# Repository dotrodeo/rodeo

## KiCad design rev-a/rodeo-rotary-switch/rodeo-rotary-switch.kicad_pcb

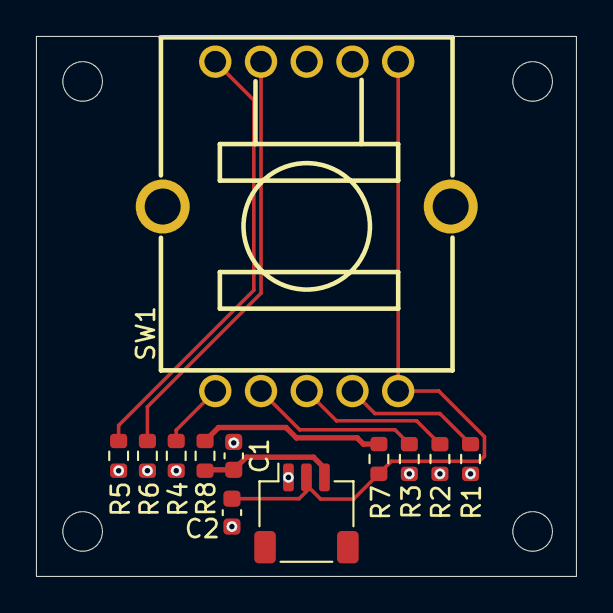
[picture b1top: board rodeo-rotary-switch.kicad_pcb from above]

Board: 2 copper layers, 30.0 x 30.0 mm, 12 parts (0 on the bottom side), 10 nets.

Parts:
C1, C2: 100n; C_0603_1608Metric
J1: Conn_01x03; JST_SH_SM03B-SRSS-TB_1x03-1MP_P1.00mm_Horizontal
R1, R8: 1K; R_0603_1608Metric
R2: 2.2K; R_0603_1608Metric
R3: 4.7K; R_0603_1608Metric
R4, R7: 10K; R_0603_1608Metric
R5: 22K; R_0603_1608Metric
R6: 47K; R_0603_1608Metric
SW1: SW-TH_SRBV141404

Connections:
3V3_D: R7.1, R8.1
GND: C1.1, C2.2, J1.1, R1.2, R2.2, R3.1, R4.1, R5.1, R6.1
unnamed: C1.2, J1.3, R8.2
unnamed: R1.1, SW1.2
unnamed: R2.1, SW1.3
unnamed: R3.2, SW1.4
unnamed: R4.2, SW1.5
unnamed: R5.2, SW1.6
unnamed: R6.2, SW1.7
OUTPUT: C2.1, J1.2, R7.2, SW1.1, SW1.10

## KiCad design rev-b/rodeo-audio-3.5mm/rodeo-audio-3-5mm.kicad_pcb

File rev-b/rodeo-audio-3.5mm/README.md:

# Rodeo audio jack board: 3.5 mm

Four stereo 3.5 mm TRS jacks for the motherboard's eight audio signals, on the
2×10 audio ribbon (motherboard J4). Passive apart from protection: every input
gets a series resistor and a clamp, every jack contact an ESD diode. The ribbon
contract is in [`rev-b.md`, "Audio interface and jack board"](../rodeo-motherboard/docs/rev-b.md#audio-interface-and-jack-board).

Designed 2026-10-14. A 1/4" variant will share this circuit with different
jacks. JLC stocks no right-angle 1/4" PCB jacks, so that board's jacks will be
hand-soldered.

```
            ┌──────────────── jack board ─────────────────┐
 ribbon     │                                             │   panel
 pin 2  ────┼── 100 Ω ──┬─────────────────── J2 tip       │   SEED OUT
 pin 4  ────┼── 100 Ω ──┼─┬───────────────── J2 ring      │
            │          TVS TVS                            │
 pin 6  ────┼───────────┬─────────────────── J3 tip       │   CODEC OUT
 pin 8  ────┼───────────┼─┬───────────────── J3 ring      │
            │          TVS TVS                            │
 pin 12 ────┼──┬────────── 470 Ω ─────────── J4 tip       │   SEED IN
 pin 14 ────┼──┼─┬──────── 470 Ω ─────────── J4 ring      │
            │ TVS TVS                                     │
 pin 16 ────┼──┬────────── 470 Ω ─────────── J5 tip       │   CODEC IN
 pin 18 ────┼──┼─┬──────── 470 Ω ─────────── J5 ring      │
            │ TVS TVS                                     │
 odd pins ──┼── GND ─────────────────────── all sleeves   │
            └─────────────────────────────────────────────┘
```

## Signals and levels

All eight signals are single-ended, about 4 Vpp at the jack, AC-coupled on the
motherboard side. Tip is left (channel 1 / A), ring is right (channel 2 / B).

A mono plug in a stereo jack grounds the ring: on an input the right channel
reads 0 V (firmware can copy left to right if it wants mono-to-both); on an
output it shorts the right output to ground, which the series resistors make
harmless (100 Ω here on the Seed outputs, 560 Ω on the motherboard for the codec).

## Connections

**J1, ribbon: 2×10 shrouded box header, DC3-2.54-20PAS (C2977593)**, the same
part as the motherboard's J4. Symbol `Connector_Generic:Conn_02x10_Odd_Even`,
footprint `Connector_IDC:IDC-Header_2x10_P2.54mm_Vertical`.

| Pin | Net | Pin | Net |
|---|---|---|---|
| 1, 3 … 19 | `GND` (all odd pins) | | |
| 2 | `AUDIO_OUT_1` | 12 | `JACK_IN_1` |
| 4 | `AUDIO_OUT_2` | 14 | `JACK_IN_2` |
| 6 | `CODEC2_OUT_A` | 16 | `CODEC2_IN_A` |
| 8 | `CODEC2_OUT_B` | 18 | `CODEC2_IN_B` |
| 10 | `+5V_A`: not used here, no connect | 20 | no connect |

**Jacks J2–J5: PJ-320D (C431535)**, the 3.5 mm stereo jack Rev A used. Symbol
`Connector_Audio:AudioJack4`, footprint
`Connector_Audio:Jack_3.5mm_PJ320D_Horizontal`. Pin R2 (the ring's switch
contact) is unused: no connect.

| Jack | Panel label | T (left) | R1 (right) | S |
|---|---|---|---|---|
| J2 | SEED OUT | R1 100 Ω from `AUDIO_OUT_1` | R2 100 Ω from `AUDIO_OUT_2` | `GND` |
| J3 | CODEC OUT | `CODEC2_OUT_A` direct | `CODEC2_OUT_B` direct | `GND` |
| J4 | SEED IN | R4 470 Ω to `JACK_IN_1` | R3 470 Ω to `JACK_IN_2` | `GND` |
| J5 | CODEC IN | R6 470 Ω to `CODEC2_IN_A` | R5 470 Ω to `CODEC2_IN_B` | `GND` |

**Protection: D1–D8, PESD3V3S1BA (C7472904)**, bidirectional 3.3 V ESD diodes,
SOD-323, 18 pF. Symbol `Device:D_TVS` (bidirectional, so orientation doesn't
matter), footprint `Diode_SMD:D_SOD-323`. Each to `GND`:

| Diode | Node | Diode | Node |
|---|---|---|---|
| D1 | J2 tip (at the jack) | D5 | `JACK_IN_2` (ribbon side of R3) |
| D2 | J2 ring (at the jack) | D6 | `JACK_IN_1` (ribbon side of R4) |
| D3 | J3 tip (at the jack) | D7 | `CODEC2_IN_B` (ribbon side of R5) |
| D4 | J3 ring (at the jack) | D8 | `CODEC2_IN_A` (ribbon side of R6) |

* **Inputs: resistor first, then the clamp.** ESD and any sustained
  out-of-range signal (a ±12 V Eurorack output) go through the 470 Ω before the
  diode clamps at about ±5.6 V, so the diode never sees more than
  (12 − 5.6) / 470 ≈ 14 mA and the motherboard side never more than ±5.6 V.
  R3–R6 are **0603** for the ESD pulse and the ≈90 mW of that worst case.
* **470 Ω on the inputs** costs ≈0.5 dB on the codec inputs (7.5 kΩ input
  resistor on the motherboard). The Seed's input impedance hasn't been measured,
  but it is several kΩ at least, so the loss there is similar or smaller.
* **Outputs:** the 3.3 V diode doesn't conduct below ±5 V, above the 4 Vpp
  (±2 V) full scale. 18 pF against the 100 Ω/560 Ω source is a pole in the MHz.
* **100 Ω on the Seed outputs** (rev-b.md "Filtering on audio I/O") protects
  them against a mono plug or a shorted cable and isolates cable capacitance.
  The codec outputs already have 560 Ω on the motherboard.

## Parts

| Part | Refs | Qty | LCSC |
|---|---|---|---|
| DC3-2.54-20PAS 2×10 box header | J1 | 1 | C2977593 |
| PJ-320D 3.5 mm stereo jack | J2–J5 | 4 | C431535 |
| PESD3V3S1BA | D1–D8 | 8 | C7472904 |
| 100 Ω 0402 | R1, R2 | 2 | C25076 |
| 470 Ω 0603 | R3–R6 | 4 | C23179 |

All in stock at JLC on 2026-10-14.

## Layout

* **J1 has the same orientation as the motherboard's J4 (rotation −90°):**
  the GND row and the key face the jacks, the signal row faces the front of the
  synth, and pin 1 is at the right-hand end in KiCad's top view. Both boards
  have their top edge toward the back panel, so identical orientations let a
  standard ribbon (both sockets crimped the same way) run flat between them with
  no twist. Turned 180°, the ribbon would need a half twist to keep pin 1 to
  pin 1. The keyed headers stop a wrong plug-in either way.
* **Panel order follows the ribbon:** in KiCad's top view, left to right CODEC
  IN, SEED IN, CODEC OUT, SEED OUT (J5, J4, J3, J2), so with pin 1 on the right
  every signal runs straight from header to jack. Seen from behind the synth
  this reads SEED OUT, CODEC OUT, SEED IN, CODEC IN, left to right.
* **Outline 60 × 30 mm**, jacks on 11.05 mm centres (x = 13.4, 24.45, 35.5,
  46.55) along the I/O edge, the box header behind them, M3 holes at (5, 15) and
  (55, 15) just outside the jack row. Check with
  `tools/kicad/grid_check.py rodeo-audio-3-5mm.kicad_pcb --rear top`.
* **Jack depth:** each PJ-320D's body is flush with the I/O edge (footprint at
  y = 6.375) and its 2 mm collar runs into the panel. Grid check reports that
  collar as ≈+1.85 mm of overhang, which is right for these jacks. The panel
  needs a Ø9 × 1 mm counterbore at each jack so plugs seat fully; see the
  mounting README's [Back panel cut-outs](../mounting/README.md#back-panel-cut-outs).
* **3D model:** KiCad has none for the PJ-320D, so `lib/rodeo_audio.pretty`
  holds a copy of KiCad's footprint with LCSC's model (C431535) aligned to it.
* **Ground:** a solid `GND` pour on both layers, tied to every odd ribbon pin and
  every sleeve. This board has no other ground connection: the motherboard joins
  it to its plane at J4 only, the single audio ground point. The PJ-320D is a
  plastic jack with no bushing, so a metal panel doesn't touch the sleeves.
* Output diodes (D1–D4) right at the jack contacts; input resistors right at
  the jacks with their diodes (D5–D8) just behind them. Keep each input's track
  away from the outputs'.

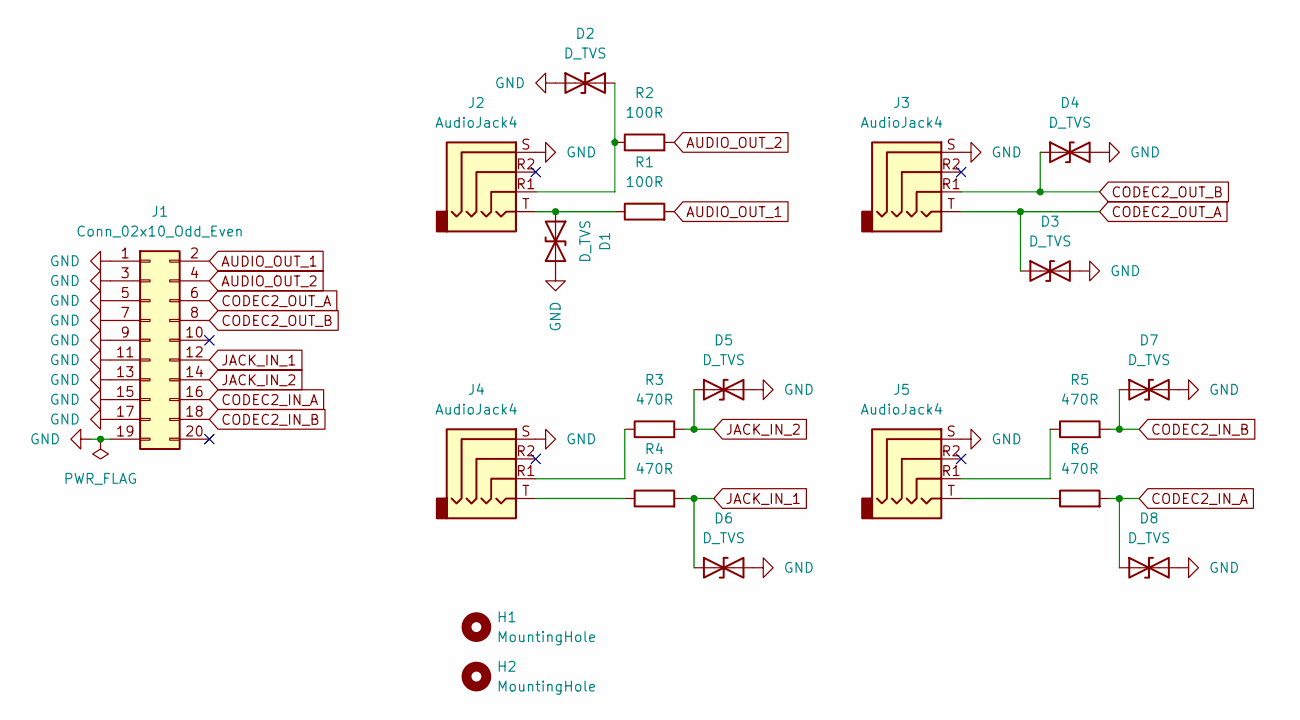
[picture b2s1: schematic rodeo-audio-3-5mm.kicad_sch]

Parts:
D1, D2, D3, D4, D5, D6, D7, D8: D_TVS; D_SOD-323; LCSC Part C7472904
H1, H2: MountingHole; MountingHole_3.2mm_M3
J1: Conn_02x10_Odd_Even; IDC-Header_2x10_P2.54mm_Vertical; LCSC Part C2977593
J2, J3, J4, J5: AudioJack4; Jack_3.5mm_PJ320D_Horizontal; LCSC Part C431535
R1, R2: 100R; R_0402_1005Metric; LCSC Part C25076
R3, R4, R5, R6: 470R; R_0603_1608Metric; LCSC Part C23179

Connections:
AUDIO_OUT_1: J1.2, R1.2
AUDIO_OUT_2: J1.4, R2.2
CODEC2_IN_A: D8.1 (A1), J1.16, R6.2
CODEC2_IN_B: D7.1 (A1), J1.18, R5.2
CODEC2_OUT_A: D3.1 (A1), J1.6, J3.T
CODEC2_OUT_B: D4.1 (A1), J1.8, J3.R1
GND: D1.2 (A2), D2.1 (A1), D3.2 (A2), D4.2 (A2), D5.2 (A2), D6.2 (A2), D7.2 (A2), D8.2 (A2), J1.1, J1.3, J1.5, J1.7, J1.9, J1.11, J1.13, J1.15, J1.17, J1.19, J2.S, J3.S, J4.S, J5.S
JACK_IN_1: D6.1 (A1), J1.12, R4.2
JACK_IN_2: D5.1 (A1), J1.14, R3.2
unnamed: D1.1 (A1), J2.T, R1.1
unnamed: D2.2 (A2), J2.R1, R2.1
unnamed: J4.R1, R3.1
unnamed: J4.T, R4.1
unnamed: J5.R1, R5.1
unnamed: J5.T, R6.1

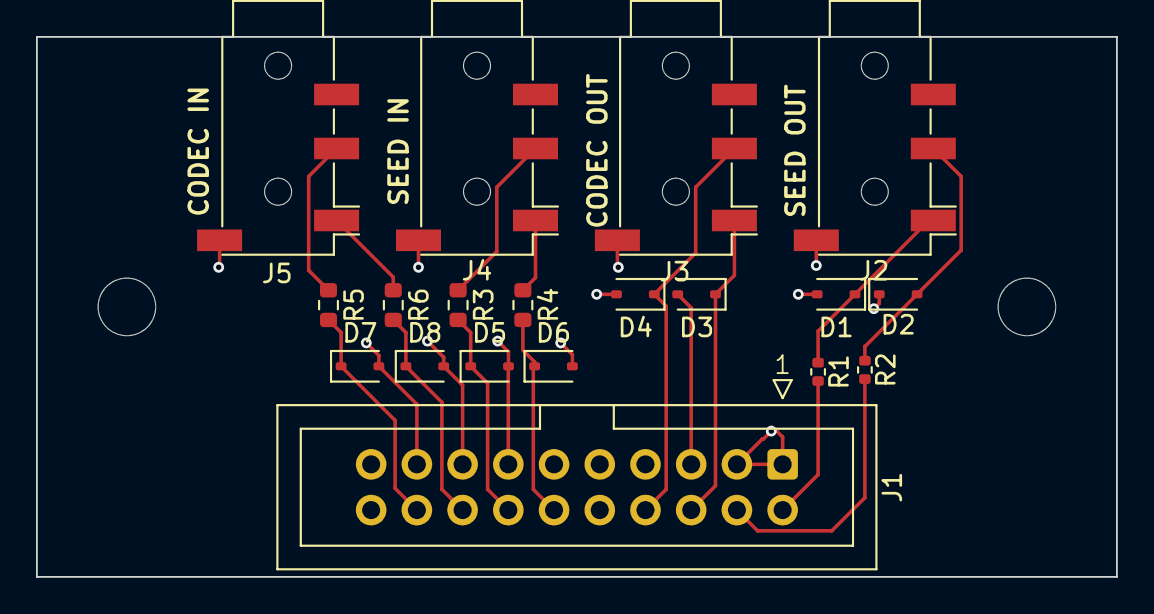
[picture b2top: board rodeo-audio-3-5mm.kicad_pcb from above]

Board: 2 copper layers, 60.0 x 30.0 mm, 21 parts (0 on the bottom side), 15 nets.

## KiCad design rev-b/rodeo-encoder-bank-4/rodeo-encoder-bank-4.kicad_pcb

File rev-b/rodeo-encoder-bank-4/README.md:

# Rodeo satellite: encoder bank ×4

Four 12 mm rotary encoders with push switches, in a row on 25 mm centres, read by
one CH32V003 on the satellite chain. The second Rev B satellite, built like the
[pot bank](../rodeo-pot-bank-4/README.md) so the two sit side by side on one panel
with their knobs at the same height. Wire contract:
[`RODEO_SATELLITE_CHAIN_CONTRACT.md`](../rodeo-motherboard/docs/RODEO_SATELLITE_CHAIN_CONTRACT.md).

Specified 2026-10-14; schematic drawn 2026-10-14.

## Board

Same construction as the pot bank:

* **Top side (faces the panel): the four encoders only**, through-hole, on 25 mm
  centres. The board hangs from the panel on the encoders' M7 bushings and nuts.
* **Bottom side: everything else**, all SMD: the MCU, IN and OUT connectors
  (vertical JST SH, cables leave from the back), the reverse-mount status LED and
  the passives. One SMD side; the encoders are through-hole on top.
* **Outline 20 × 100 mm**, matching the pot bank. Shafts at x = 9.9 mm and
  9.7, 34.7, 59.7 and 84.7 mm along the board (A–B pin rows at 17.2, 42.2, 67.2,
  92.2): 1.53 mm further along than the pot bank's shafts, which is fine for
  boards that sit apart on the panel.

## Encoders ENC1–ENC4: Bourns PEC11R-4215F-S0024 (C143790)

12 mm, 24 detents and 24 pulses per revolution (one full quadrature cycle per
detent), momentary push switch, 6 mm flatted shaft, threaded bushing for panel
mounting. 5,622 in stock at JLC on 2026-10-14.

* **Footprint `rodeo_encoder_bank:RotaryEncoder_Bourns_PEC11R-S_Vertical`**: KiCad's
  `RotaryEncoder_Alps_EC11E-Switch_Vertical_H20mm` with LCSC's PEC11R model
  attached (KiCad has no PEC11R footprint or model). The PEC11R's pattern matches:
  A, C, B on a 2.5 mm row, the switch pins 14.5 mm across, the shaft 7.5 mm from the
  A–B row. Its lugs are 11.4 mm apart against the footprint's 11.2 mm slots,
  which the 2.8 mm slots absorb. Checked by exporting a test board with the model
  and measuring where its pins and lugs come through.
* **Symbol `Device:RotaryEncoder_Switch_MP`**: pins A, B, C (common), S1, S2, and MP
  for the lugs.
* **Heights** (from the model): mounting face 6.5 mm above the PCB, shaft tip
  21.5 mm, so **15 mm of shaft above the mounting face, the same as the pot bank's
  RK09L**. Both boards hang from the panel at their mounting faces, so their knobs
  end up level.
* **Bushing:** M7 × 0.75 per the PEC11R family drawing (the model shows a 6.5 mm
  threaded section). **Confirm against the Bourns datasheet before drawing the
  panel**: panel hole Ø7.5 mm. Bourns' datasheet PDF wouldn't extract here.

## Pin budget: why the switches share one ADC pin

Four encoders need 12 inputs (A, B and switch each). The CH32V003F4P6 has 16
general-purpose pins once SWIO (PD1) and NRST (PD7) are set aside, and the chain
already takes 6 of them (two RX, two TX, `PRESENT`, the ID). The fix:

* **The four push switches share one ADC pin through a binary-weighted ladder.**
  The pin is pulled up by 10 kΩ; each switch pulls it toward GND through its own
  resistor (10 k, 20 k, 40.2 k, 80.6 k). All 16 combinations land on distinct ADC
  levels, at least 16 counts apart on the 10-bit ADC, so any set of pressed
  switches decodes. With nothing pressed the ladder draws nothing.
* **The ID divider's top resistor goes to `+3V3`** rather than a GPIO, which the
  contract allows (§1.6). It costs 0.2 mA.

That leaves exactly the 10 pins needed for 8 encoder lines, `PRESENT` and the LED.
Firmware polls A/B from a timer (≥2 kHz; a fast hand turn is ≈500 edges/s) with
a quadrature state machine, which also rejects contact bounce. EXTI isn't used:
the CH32V003 shares one interrupt line per pin number across ports.

## MCU: CH32V003F4P6 (C5187096), TSSOP-20

Symbol `MCU_WCH_RiscV:CH32V003FxPx`. Ring closing and connectors exactly as on
the pot bank (USART1 mapping 0 normally, mapping 3 when last; IN `DATA_FWD` on
both PD6 and PC1).

| Pin | Name | Connection |
|---|---|---|
| 9 | VDD | `+3V3`; C4 100 nF and C3 1 µF to `GND` at the pin |
| 7 | VSS | `GND` |
| 3 | PD6 | `SAT_RX`: J1 IN pin 3 |
| 11 | PC1 | `SAT_RX` (same net) |
| 2 | PD5 | R4 33 Ω → J2 OUT pin 3 |
| 10 | PC0 | R2 33 Ω → `DATA_RET` |
| 19 | PD2 | `PRESENT`: J2 OUT pin 5 (internal pull-up) |
| 20 | PD3 (A4) | `ID`: R3 10 kΩ from `+3V3`, R5 6.65 kΩ (R_ID, kind 6) to `GND` |
| 1 | PD4 (A7) | `SW_SENSE`: R6 10 kΩ from `+3V3`, C5 10 nF to `GND`, the switch ladder |
| 5 | PA1 | `ENC1_A` |
| 6 | PA2 | `ENC1_B` |
| 12 | PC2 | `ENC2_A` |
| 13 | PC3 | `ENC2_B` |
| 14 | PC4 | `ENC3_A` |
| 15 | PC5 | `ENC3_B` |
| 16 | PC6 | `ENC4_A` |
| 17 | PC7 | `ENC4_B` |
| 8 | PD0 | R1 1.5 kΩ → D1 status LED anode; cathode to `GND` |
| 18 | PD1 | `SWIO`: programming pad |
| 4 | PD7 | `NRST`: programming pad |

No spare pins.

## Encoder wiring

For each encoder n (1–4):

| Encoder pin | Connection |
|---|---|
| C (common) | `GND` |
| A | `ENCn_A`: 22 kΩ to `+3V3`, 4.7 nF to `GND` at the MCU pin |
| B | `ENCn_B`: 22 kΩ to `+3V3`, 4.7 nF to `GND` at the MCU pin |

(Schematic: encoders SW1–SW4; pull-ups R8/R9, R10/R12, R13/R15, R16/R18 and caps
C6/C7, C8/C9, C10/C11, C12/C13 for encoders 1–4, A then B.)
| S1 | `GND` |
| S2 | ladder resistor to `SW_SENSE`: SW1 R7 10.0 kΩ, SW2 R11 20.0 kΩ, SW3 R14 40.2 kΩ, SW4 R17 80.6 kΩ (1 %) |
| MP (lugs) | `GND`: the bushings touch the panel, so ESD from a knob goes straight to ground |

* **22 kΩ pull-ups** draw 0.15 mA per closed contact, so even with all eight
  resting closed the board stays inside its 6 mA budget. With the 4.7 nF caps
  the rise time is ≈0.1 ms, well under the ≈2 ms between edges on a fast turn.
* **Ladder levels** (10 kΩ pull-up, ADC full scale 1023), for the firmware's
  decode table: none 1023; ENC4 910; ENC3 819; ENC3+4 745; ENC2 682; … ENC1 512; … all four
  356 (minimum gap 16 counts). The firmware takes the nearest of the 16 computed levels.

## Connectors, ID, LED, programming

As on the pot bank:

* **J1 IN, J2 OUT**: BM05B-SRSS-TB (C160391), vertical, bottom side; pin table in
  the pot bank README. `+3V3` and `GND` pass straight from J1 to J2: route them
  as 1 mm tracks or solid pours (the pot bank review found 0.2 mm tracks there
  eat most of the chain's voltage budget).
* **Board kind 6, `encoder bank ×4`, R_ID 6.65 kΩ.** Four `ENCODER` slots,
  encoders 1–4 in order; output slot 1 is `LED`, slots 2–4 `NONE`.
* **D1**: LTST-C230KRKT (C125107), reverse-mount through the board, footprint
  `rodeo_encoder_bank:LED_1206_3216Metric_ReverseMount_Hole1.8x2.4mm`.
* **J3**: SWIO, `+3V3`, `GND`, NRST pads, not fitted, excluded from the BOM.

## Power

MCU ≈2–3 mA, LED 0.8 mA, ID divider 0.2 mA, encoder pull-ups 0–1.2 mA, ladder
0–0.5 mA while pressing: within the 6 mA per-satellite budget.

## Parts

| Part | Refs | Qty | LCSC |
|---|---|---|---|
| PEC11R-4215F-S0024 | SW1–SW4 | 4 | C143790 |
| CH32V003F4P6 | U1 | 1 | C5187096 |
| BM05B-SRSS-TB | J1, J2 | 2 | C160391 |
| LTST-C230KRKT | D1 | 1 | C125107 |
| 100 nF 0402 | C4 | 1 | C1525 |
| 1 µF 0402 | C3 | 1 | C52923 |
| 10 nF 0402 | C5 | 1 | C15195 |
| 4.7 nF 0402 | C6–C13 | 8 | C1538 |
| 33 Ω 0603 | R2, R4 | 2 | C23140 |
| 10 kΩ 0603 | R3, R6, R7 | 3 | C25804 |
| 6.65 kΩ 0603 1 % | R5 | 1 | C60344 |
| 1.5 kΩ 0603 | R1 | 1 | C22843 |
| 22 kΩ 0603 | R8–R10, R12, R13, R15, R16, R18 | 8 | C31850 |
| 20.0 kΩ 0603 1 % | R11 | 1 | C4184 |
| 40.2 kΩ 0603 1 % | R14 | 1 | C12447 |
| 80.6 kΩ 0603 1 % | R17 | 1 | C23249 |

All in stock at JLC on 2026-10-14.

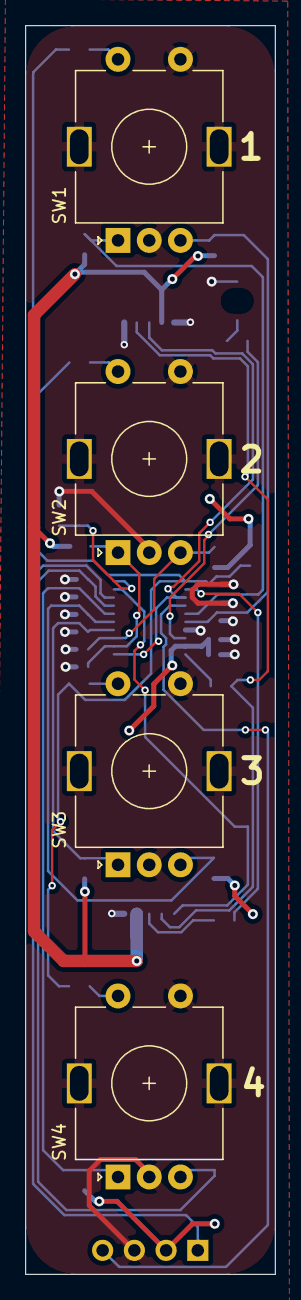
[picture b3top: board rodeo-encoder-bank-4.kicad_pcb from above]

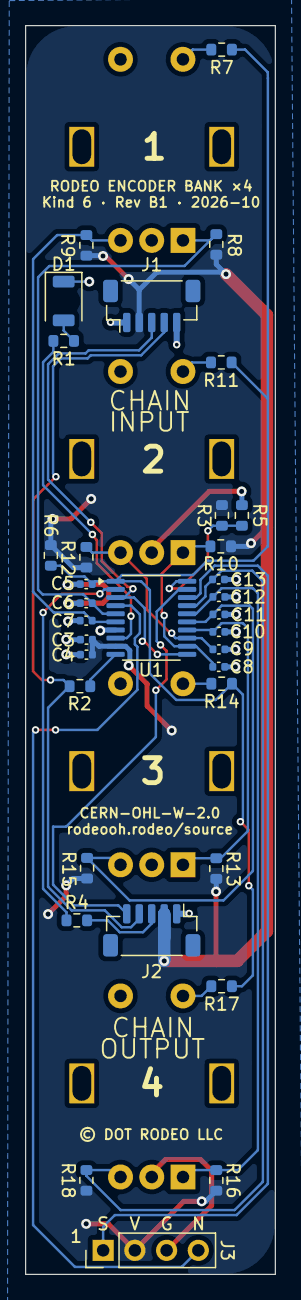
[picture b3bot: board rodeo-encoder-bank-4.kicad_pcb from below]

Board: 2 copper layers, 20.0 x 100.0 mm, 38 parts (34 on the bottom side), 26 nets.

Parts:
C3: 1u; C_0402_1005Metric
C4: 100n; C_0402_1005Metric
C5: 10n; C_0402_1005Metric
C6, C7, C8, C9, C10, C11, C12, C13: 4.7n; C_0402_1005Metric
D1: LED; LED_1206_3216Metric_ReverseMount_Hole1.8x2.4mm
J1, J2: Conn_01x05; JST_SH_BM05B-SRSS-TB_1x05-1MP_P1.00mm_Vertical
J3: Conn_01x04; PinHeader_1x04_P2.54mm_Vertical
R1: 1K5; R_0603_1608Metric
R2, R4: 33R; R_0603_1608Metric
R3, R6, R7: 10K; R_0603_1608Metric
R5: 6K65; R_0603_1608Metric
R8, R9, R10, R12, R13, R15, R16, R18: 22K; R_0603_1608Metric
R11: 20K; R_0603_1608Metric
R14: 40K2; R_0603_1608Metric
R17: 80K6; R_0603_1608Metric
SW1, SW2, SW3, SW4: RotaryEncoder_Switch_MP; RotaryEncoder_Bourns_PEC11R-S_Vertical
U1: CH32V003FxPx; TSSOP-20_4.4x6.5mm_P0.65mm

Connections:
+3V3: C3.2, C4.2, J1.2, J2.2, J3.2, R3.2, R6.1, R8.1, R9.2, R10.1, R12.2, R13.1, R15.2, R16.1, R18.2, U1.9 (VDD)
DATA_RET: J1.4, J2.4, R2.1
ENC1_A: C6.1, R8.2, SW1.A, U1.5 (PA1)
ENC1_B: C7.2, R9.1, SW1.B, U1.6 (PA2)
ENC2_A: C8.1, R10.2, SW2.A, U1.12 (PC2)
ENC2_B: C9.2, R12.1, SW2.B, U1.13 (PC3)
ENC3_A: C10.1, R13.2, SW3.A, U1.14 (PC4)
ENC3_B: C11.2, R15.1, SW3.B, U1.15 (PC5)
ENC4_A: C12.1, R16.2, SW4.A, U1.16 (PC6)
ENC4_B: C13.2, R18.1, SW4.B, U1.17 (PC7)
GND: C3.1, C4.1, C5.2, C6.2, C7.1, C8.2, C9.1, C10.2, C11.1, C12.2, C13.1, D1.1 (K), J1.1, J1.5, J2.1, J3.3, R5.1, SW1.C, SW1.MP, SW1.S1, SW2.C, SW2.MP, SW2.S1, SW3.C, SW3.MP, SW3.S1, SW4.C, SW4.MP, SW4.S1, U1.7 (VSS)
NRST: J3.4, U1.4 (PD7)
unnamed: D1.2 (A), R1.1
unnamed: J2.3, R4.2
unnamed: R7.2, SW1.S2
unnamed: R11.2, SW2.S2
unnamed: R14.2, SW3.S2
unnamed: R17.2, SW4.S2
unnamed: R2.2, U1.10 (PC0)
unnamed: R1.2, U1.8 (PD0)
unnamed: R3.1, R5.2, U1.20 (PD3)
unnamed: R4.1, U1.2 (PD5)
PRESENT: J2.5, U1.19 (PD2)
SAT_RX: J1.3, U1.3 (PD6), U1.11 (PC1)
SWIO: J3.1, U1.18 (PD1)
SW_SENSE: C5.1, R6.2, R7.1, R11.1, R14.1, R17.1, U1.1 (PD4)

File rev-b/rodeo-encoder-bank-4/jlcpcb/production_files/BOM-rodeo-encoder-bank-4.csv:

Comment,Designator,Footprint,LCSC,Quantity
1u,C3,C_0402_1005Metric,C52923,1
100n,C4,C_0402_1005Metric,C1525,1
10n,C5,C_0402_1005Metric,C15195,1
4.7n,"C6,C7,C8,C9,C10,C11,C12,C13",C_0402_1005Metric,C1538,8
LED,D1,LED_1206_3216Metric_ReverseMount_Hole1.8x2.4mm,C125107,1
Conn_01x05,"J1,J2",JST_SH_BM05B-SRSS-TB_1x05-1MP_P1.00mm_Vertical,C160391,2
1K5,R1,R_0603_1608Metric,C22843,1
33R,"R2,R4",R_0603_1608Metric,C23140,2
10K,"R3,R6,R7",R_0603_1608Metric,C25804,3
6K65,R5,R_0603_1608Metric,C60344,1
22K,"R8,R9,R10,R12,R13,R15,R16,R18",R_0603_1608Metric,C31850,8
20K,R11,R_0603_1608Metric,C4184,1
40K2,R14,R_0603_1608Metric,C12447,1
80K6,R17,R_0603_1608Metric,C23249,1
RotaryEncoder_Switch_MP,"SW1,SW2,SW3,SW4",RotaryEncoder_Bourns_PEC11R-S_Vertical,C143790,4
CH32V003FxPx,U1,TSSOP-20_4.4x6.5mm_P0.65mm,C5187096,1

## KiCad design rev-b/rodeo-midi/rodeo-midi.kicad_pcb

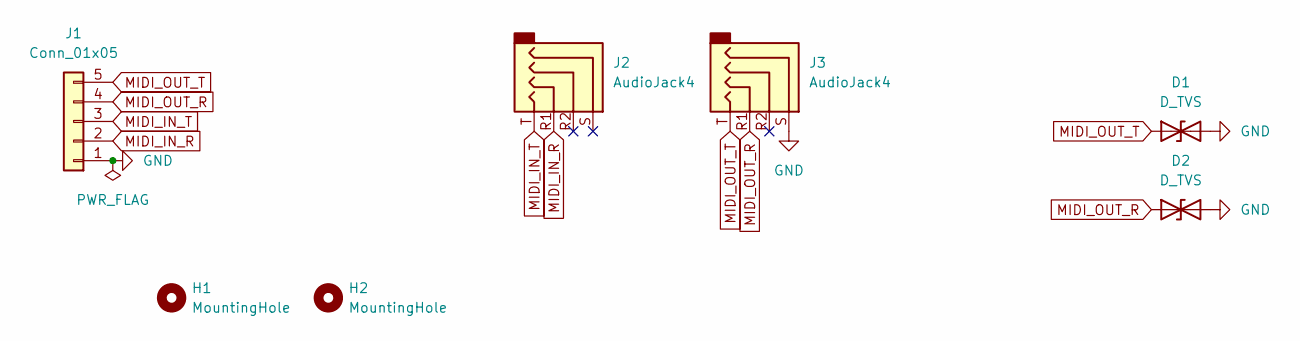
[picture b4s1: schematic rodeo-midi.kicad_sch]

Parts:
D1, D2: D_TVS; D_SOD-323; LCSC Part C7472904
H1, H2: MountingHole; MountingHole_3.2mm_M3
J1: Conn_01x05; JST_SH_BM05B-SRSS-TB_1x05-1MP_P1.00mm_Vertical; LCSC Part C160391
J2, J3: AudioJack4; Jack_3.5mm_PJ320D_Horizontal; LCSC Part C431535

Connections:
GND: D1.2 (A2), D2.2 (A2), J1.1, J3.S
MIDI_IN_R: J1.2, J2.R1
MIDI_IN_T: J1.3, J2.T
MIDI_OUT_R: D2.1 (A1), J1.4, J3.R1
MIDI_OUT_T: D1.1 (A1), J1.5, J3.T

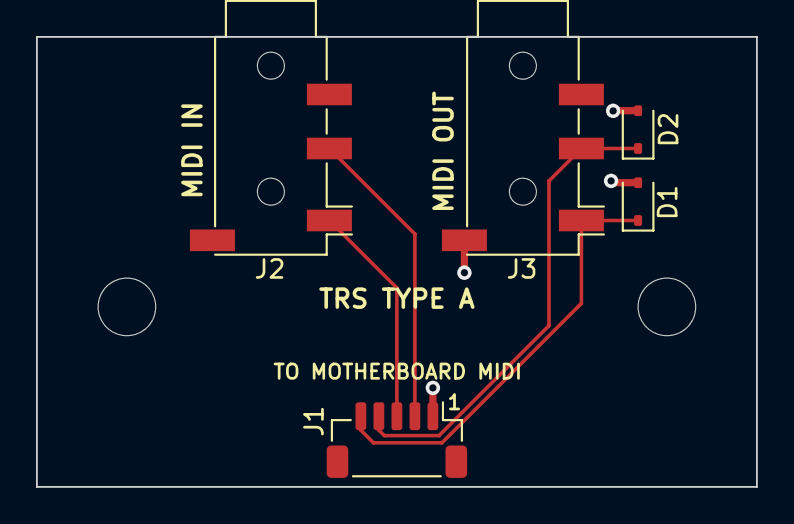
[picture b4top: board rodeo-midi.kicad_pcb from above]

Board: 2 copper layers, 40.0 x 25.0 mm, 7 parts (0 on the bottom side), 5 nets.

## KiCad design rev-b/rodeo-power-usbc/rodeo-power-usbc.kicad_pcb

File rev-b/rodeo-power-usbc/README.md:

# Rodeo power board: USB-C

The default Rev B power input: a USB-C jack on a small board behind the panel,
cabled to the motherboard's power input (J2). It carries 5 V, USB data for the
Seed (USB-MIDI, audio, DFU flashing) and the charger's status LEDs. The
contract it meets is in [`rev-b.md`, "Power"](../rodeo-motherboard/docs/rev-b.md#power).

Designed 2026-10-12. Mounting: the jack and the LEDs sit on the I/O edge and come
through panel cut-outs; the 40 × 20 mm board sits on the
[rear rail](../mounting/README.md) on two M3 × 8 mm standoffs.

## Connections

**J1, USB-C receptacle (HRO TYPE-C-31-M-12, C165948).** Symbol
`Connector:USB_C_Receptacle_USB2.0_16P`, footprint
`Connector_USB:USB_C_Receptacle_HRO_TYPE-C-31-M-12`.

| J1 pin | Net | Notes |
|---|---|---|
| A4, A9, B4, B9 (VBUS) | `VBUS` | |
| A1, A12, B1, B12 (GND), SH (shield) | `GND` | |
| A5 (CC1) | R1 5.1 kΩ to `GND` | marks the board as a sink: 5 V only, no USB-PD |
| B5 (CC2) | R2 5.1 kΩ to `GND` | |
| A6, B6 (D+) | `USB_DP_JACK` | both rows tied, for either plug orientation |
| A7, B7 (D−) | `USB_DN_JACK` | |
| A8, B8 (SBU) | no connect | |

**Protection, at the jack.**

| Part | Connection |
|---|---|
| U1 USBLC6-2SC6 (C7519), flow-through | pin 1 ← `USB_DN_JACK`, pin 6 → `USB_DN`; pin 3 ← `USB_DP_JACK`, pin 4 → `USB_DP`; pin 5 `VBUS`; pin 2 `GND` |
| D1 SMF5.0A TVS (C193402) | cathode `VBUS`, anode `GND` |
| C1 4.7 µF 25 V 0603 (C69335) | `VBUS` to `GND` |

**J2, to the motherboard: JST PH 8-pin vertical, B8B-PH-K-S (C157974).**
Same pin numbers as the motherboard's J2, so a standard PH cable (pin 1 to
pin 1) connects them. Pin 1 is at the right as seen in KiCad (I/O edge at the
top). The motherboard's J2 faces the front of the case, so the cable leaves it
forward and folds back to this board; with pin 1 here on that side, the cable
arrives without a twist.

| J2 pin | Net |
|---|---|
| 1, 6 | `VBUS` |
| 2, 5 | `GND` |
| 3 | `USB_DN` |
| 4 | `USB_DP` |
| 7 | `~PGOOD` |
| 8 | `~CHG` |

**Status LEDs: side-view LiteOn LTST-S220, at the panel edge.** Symbol
`Device:LED`, footprint `rodeo_power:LED_LiteOn_LTST-S220_SideView`. The lens is
on the side the silkscreen bracket wraps (the courtyard bulges there too); put
that side at the board edge.

| Part | Anode | Cathode |
|---|---|---|
| D2 green LTST-S220KGKT (C160469), power good | R3 1 kΩ to `VBUS` | `~PGOOD` (J2 pin 7) |
| D3 red LTST-S220KRKT (C284935), charging | R4 1 kΩ to `VBUS` | `~CHG` (J2 pin 8) |

≈3 mA each. Both light only with USB plugged in: power good when the
motherboard's charger accepts the input, red while the cell charges.

**Mounting:** two M3 holes (`MountingHole:MountingHole_3.2mm_M3`) at (5, 15)
and (35, 15) mm from the I/O edge's left end: rail row 1, 30 mm apart.

## Parts

| Part | Qty | LCSC |
|---|---|---|
| TYPE-C-31-M-12 USB-C | 1 | C165948 |
| USBLC6-2SC6 | 1 | C7519 |
| SMF5.0A | 1 | C193402 |
| 4.7 µF 25 V 0603 | 1 | C69335 |
| 5.1 kΩ 0402 | 2 | C25905 |
| 1 kΩ 0402 | 2 | C11702 |
| LTST-S220KGKT (green) | 1 | C160469 |
| LTST-S220KRKT (red) | 1 | C284935 |
| B8B-PH-K-S | 1 | C157974 |

## Layout

* J1 and both LEDs on the panel edge; J1's shell flush with the edge.
* U1 and D1 within a few mm of J1, D+/D− routed as a pair (90 Ω differential),
  short, to J2.
* The cable to the motherboard: PH 8-pin both ends, 24–26 AWG, under ≈30 cm, with
  D+/D− adjacent (they sit between the two grounds).

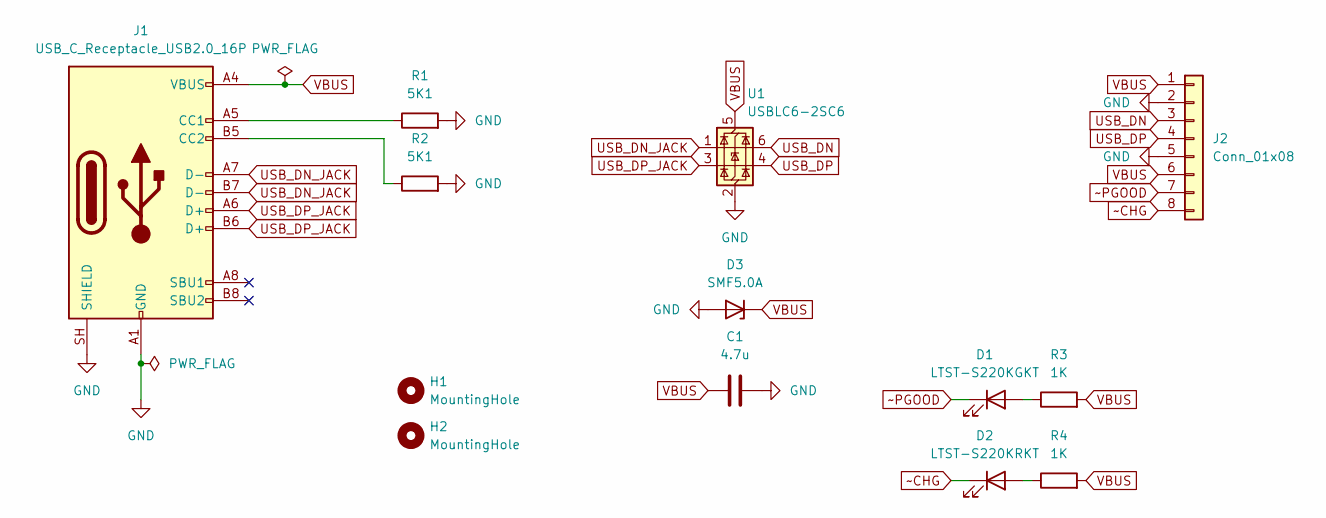
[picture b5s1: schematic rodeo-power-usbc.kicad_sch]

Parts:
C1: 4.7u; C_0603_1608Metric; LCSC Part C69335
D1: LTST-S220KGKT; LED_LiteOn_LTST-S220_SideView; LCSC Part C160469
D2: LTST-S220KRKT; LED_LiteOn_LTST-S220_SideView; LCSC Part C284935
D3: SMF5.0A; D_SOD-123F; LCSC Part C193402
H1, H2: MountingHole; MountingHole_3.2mm_M3
J1: USB_C_Receptacle_USB2.0_16P; USB_C_Receptacle_HRO_TYPE-C-31-M-12; LCSC Part C165948
J2: Conn_01x08; JST_PH_B8B-PH-K_1x08_P2.00mm_Vertical; LCSC Part C157974
R1, R2: 5K1; R_0402_1005Metric; LCSC Part C25905
R3, R4: 1K; R_0402_1005Metric; LCSC Part C11702
U1: USBLC6-2SC6; SOT-23-6; LCSC Part C7519

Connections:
GND: C1.2, D3.2 (A), J1.A1 (GND), J1.A12 (GND), J1.B1 (GND), J1.B12 (GND), J1.SH (SHIELD), J2.2, J2.5, R1.2, R2.2, U1.2 (GND)
unnamed: D1.2 (A), R3.1
unnamed: D2.2 (A), R4.1
unnamed: J1.A5 (CC1), R1.1
unnamed: J1.B5 (CC2), R2.1
USB_DN: J2.3, U1.6 (I/O1)
USB_DN_JACK: J1.A7 (D-), J1.B7 (D-), U1.1 (I/O1)
USB_DP: J2.4, U1.4 (I/O2)
USB_DP_JACK: J1.A6 (D+), J1.B6 (D+), U1.3 (I/O2)
VBUS: C1.1, D3.1 (K), J1.A4 (VBUS), J1.A9 (VBUS), J1.B4 (VBUS), J1.B9 (VBUS), J2.1, J2.6, R3.2, R4.2, U1.5 (VBUS)
~CHG: D2.1 (K), J2.8
~PGOOD: D1.1 (K), J2.7

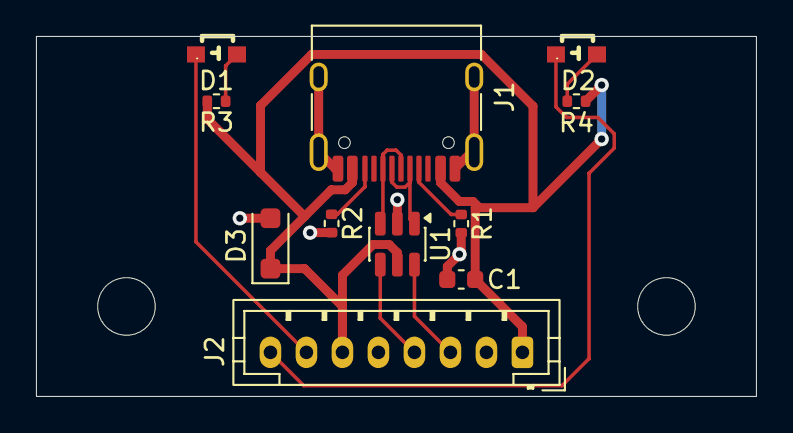
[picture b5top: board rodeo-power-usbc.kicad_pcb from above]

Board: 2 copper layers, 40.0 x 20.0 mm, 13 parts (0 on the bottom side), 12 nets.

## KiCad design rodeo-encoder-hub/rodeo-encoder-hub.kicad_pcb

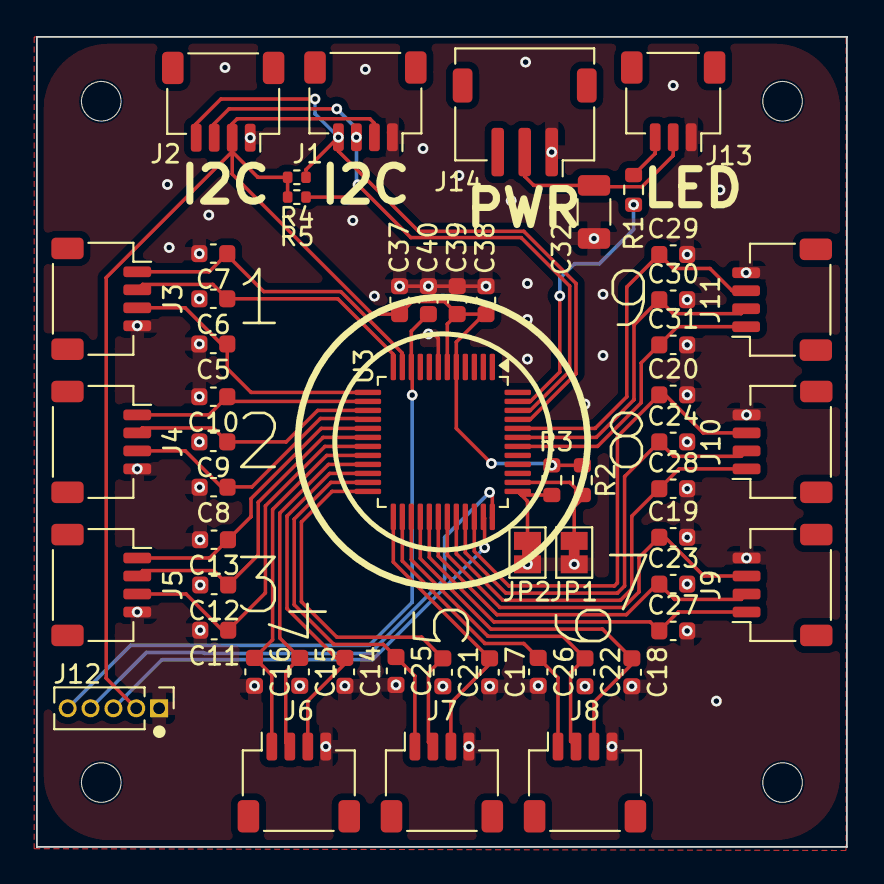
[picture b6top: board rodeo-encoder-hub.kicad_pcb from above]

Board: 2 copper layers, 45.0 x 45.0 mm, 54 parts (0 on the bottom side), 39 nets.

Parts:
C5, C6, C7, C8, C9, C10, C11, C12, C13, C14, C15, C16, C17, C18, C19, C20, C21, C22, C23, C24, C25, C26, C27, C28, C29, C30, C31: 10n; C_0603_1608Metric
C32: 100u; C_1206_3216Metric
C37, C38, C40: 100n; C_0603_1608Metric
C39: 4.7u; C_0603_1608Metric
J1, J2, J3, J4, J5, J6, J7, J8, J9, J10, J11: Conn_01x04; JST_SH_SM04B-SRSS-TB_1x04-1MP_P1.00mm_Horizontal
J12: Conn_01x05; PinHeader_1x05_P1.27mm_Vertical
J13: Conn_01x03; JST_SH_SM03B-SRSS-TB_1x03-1MP_P1.00mm_Horizontal
J14: Conn_01x03; JST_ZH_S3B-ZR-SM4A-TF_1x03-1MP_P1.50mm_Horizontal
JP1, JP2: SolderJumper_2_Bridged; SolderJumper-2_P1.3mm_Bridged_Pad1.0x1.5mm
R1: 330R; R_0603_1608Metric
R2, R3: 10K; R_0603_1608Metric
R4, R5: 2.2K; R_0402_1005Metric
U3: STM32C031C6Tx; LQFP-48_7x7mm_P0.5mm

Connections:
ENC_1_A: C7.1, J3.1, U3.11 (PA0)
ENC_1_B: C6.1, J3.2, U3.12 (PA1)
ENC_1_S: C5.1, J3.3, U3.13 (PA2)
ENC_2_A: C10.1, J4.1, U3.14 (PA3)
ENC_2_B: C9.1, J4.2, U3.15 (PA4)
ENC_2_S: C8.1, J4.3, U3.16 (PA5)
ENC_3_A: C13.1, J5.1, U3.17 (PA6)
ENC_3_B: C12.1, J5.2, U3.18 (PA7)
ENC_3_S: C11.1, J5.3, U3.19 (PB0)
ENC_4_A: C16.1, J6.1, U3.20 (PB1)
ENC_4_B: C15.1, J6.2, U3.21 (PB2)
ENC_4_S: C14.1, J6.3, U3.22 (PB10)
ENC_5_A: C25.1, J7.1, U3.23 (PB11)
ENC_5_B: C21.1, J7.2, U3.24 (PB12)
ENC_5_S: C17.1, J7.3, U3.25 (PB13)
ENC_6_A: C26.1, J8.1, U3.26 (PB14)
ENC_6_B: C22.1, J8.2, U3.27 (PB15)
ENC_6_S: C18.1, J8.3, U3.28 (PA8)
ENC_7_A: C27.1, J9.1, U3.29 (PA9)
ENC_7_B: C23.1, J9.2, U3.30 (PC6)
ENC_7_S: C19.1, J9.3, U3.31 (PC7)
ENC_8_A: C28.1, J10.1, U3.32 (PA10)
ENC_8_B: C24.1, J10.2, U3.33 (PA11)
ENC_8_S: C20.1, J10.3, U3.34 (PA12)
ENC_9_A: C31.1, J11.1, U3.42 (PB3)
ENC_9_B: C30.1, J11.2, U3.43 (PB4)
ENC_9_S: C29.1, J11.3, U3.44 (PB5)
GND: C5.2, C6.2, C7.2, C8.2, C9.2, C10.2, C11.2, C12.2, C13.2, C14.2, C15.2, C16.2, C17.2, C18.2, C19.2, C20.2, C21.2, C22.2, C23.2, C24.2, C25.2, C26.2, C27.2, C28.2, C29.2, C30.2, C31.2, C32.2, C37.2, C38.2, C39.2, C40.2, J1.1, J2.1, J3.4, J4.4, J5.4, J6.4, J7.4, J8.4, J9.4, J10.4, J11.4, J12.1, J13.1, J14.1, JP1.1 (A), JP2.1 (A), U3.7 (VSS)
I2C_ADDR_1: JP1.2 (B), R2.2, U3.38 (PD0)
I2C_ADDR_2: JP2.2 (B), R3.2, U3.37 (PA15)
LED_3V3: C32.1, J13.2, J14.2
LED_DATA: R1.2, U3.47 (PB8)
NRST: C40.1, J12.5, U3.10 (PF2)
unnamed: J13.3, R1.1
SCL: J1.4, J2.4, R4.1, U3.45 (PB6)
SDA: J1.3, J2.3, R5.1, U3.46 (PB7)
SWCLK: J12.4, U3.36 (PA14)
SWDIO: J12.3, U3.35 (PA13)
VDD: C37.1, C38.1, C39.1, J1.2, J2.2, J12.2, R2.1, R3.1, R4.2, R5.2, U3.5 (VREF+), U3.6 (VDD)

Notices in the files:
rev-b/rodeo-audio-3.5mm/rodeo-audio-3-5mm.kicad_pcb:
CERN-OHL-W-2.0
© DOT RODEO LLC
